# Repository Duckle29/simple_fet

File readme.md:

# Duckles generic PCB template

This is a sample readme for a kicad project

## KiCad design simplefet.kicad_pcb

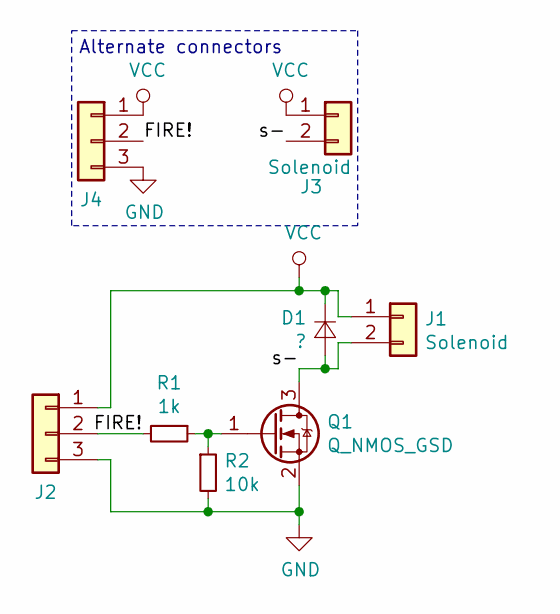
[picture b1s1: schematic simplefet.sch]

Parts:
D1: ?; D_SMA-SMB_Universal_Handsoldering
J1: Solenoid; JST_PH_S2B-PH-K_1x02_P2.00mm_Horizontal
J2: Conn_01x03; JST_PH_S3B-PH-K_1x03_P2.00mm_Horizontal
J3: Solenoid; PinHeader_1x02_P2.54mm_Vertical
J4: Conn_01x03; PinHeader_1x03_P2.54mm_Vertical
Q1: Q_NMOS_GSD; SOT-23_Handsoldering
R1: 1k; R_0603_1608Metric_Pad1.05x0.95mm_HandSolder
R2: 10k; R_0603_1608Metric_Pad1.05x0.95mm_HandSolder

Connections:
/FIRE!: J2.2, J4.2, R1.2
/s-: D1.2 (A), J1.2, J3.2, Q1.3 (D)
GND: J2.3, J4.3, Q1.2 (S), R2.2
unnamed: Q1.1 (G), R1.1, R2.1
VCC: D1.1 (K), J1.1, J2.1, J3.1, J4.1

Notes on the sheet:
Alternate connectors

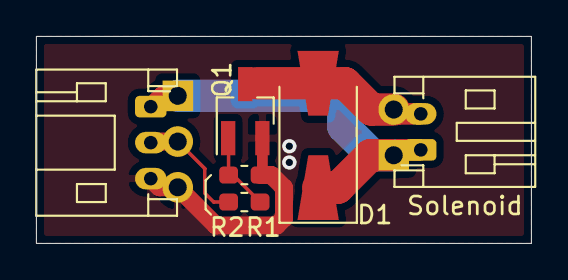
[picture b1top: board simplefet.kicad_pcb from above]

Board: 2 copper layers, 27.5 x 11.5 mm, 8 parts (0 on the bottom side), 5 nets.

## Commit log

2019-11-29 Added panelized version
